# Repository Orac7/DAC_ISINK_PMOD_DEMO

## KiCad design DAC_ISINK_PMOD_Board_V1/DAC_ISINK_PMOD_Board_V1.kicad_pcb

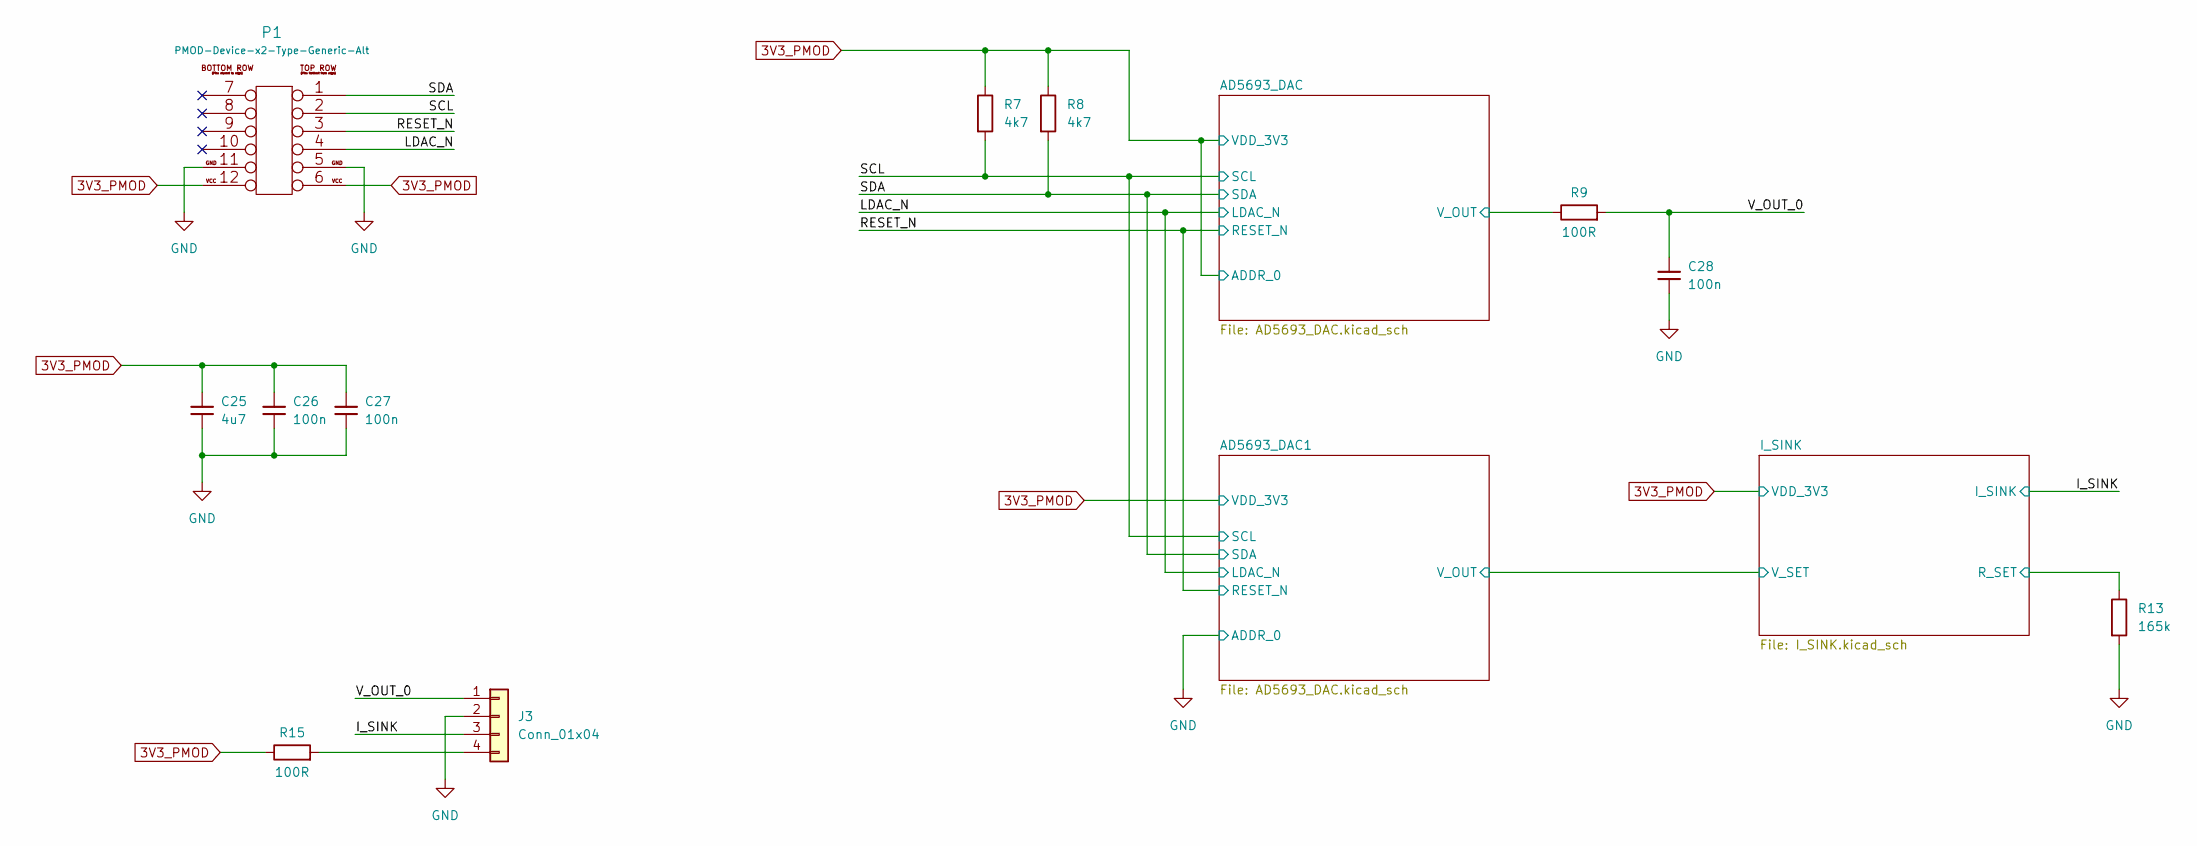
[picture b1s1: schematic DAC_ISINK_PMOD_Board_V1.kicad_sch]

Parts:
C25: 4u7; C_0603_1608Metric
C26, C27, C28: 100n; C_0603_1608Metric
J3: Conn_01x04; PhoenixContact_MC_1,5_4-G-3.5_1x04_P3.50mm_Horizontal
P1: PMOD-Device-x2-Type-Generic-Alt; pmod_pin_array_6x2
R7, R8: 4k7; R_0603_1608Metric
R9, R15: 100R; R_0603_1608Metric
R13: 165k; R_0603_1608Metric

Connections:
3V3_PMOD: C25.1, C26.1, C27.1, P1.6, P1.12, R7.1, R8.1, R15.1; also elsewhere on the board
/AD5693_DAC/V_OUT: R9.1; also elsewhere on the board
/I_SINK: J3.3; also elsewhere on the board
/I_SINK/R_SET: R13.1; also elsewhere on the board
/LDAC_N: P1.4; also elsewhere on the board
/RESET_N: P1.3; also elsewhere on the board
/SCL: P1.2, R7.2; also elsewhere on the board
/SDA: P1.1, R8.2; also elsewhere on the board
/V_OUT_0: C28.1, J3.1, R9.2
GND: C25.2, C26.2, C27.2, C28.2, J3.2, P1.5, P1.11, R13.2; also elsewhere on the board
unnamed: J3.4, R15.2

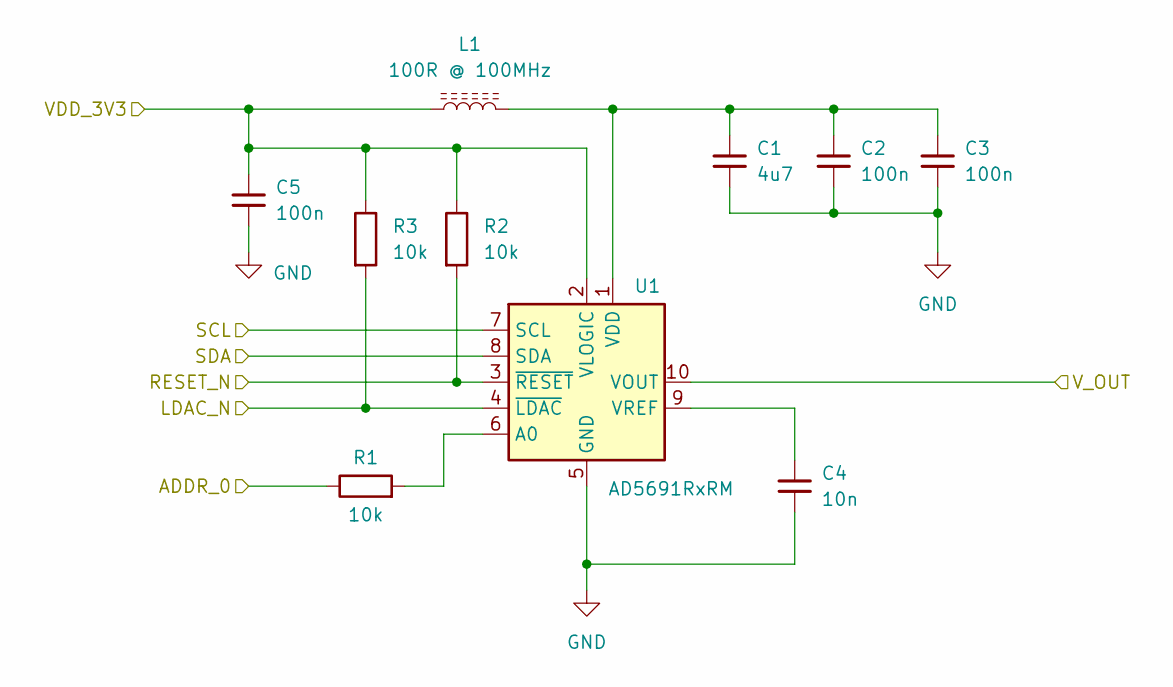
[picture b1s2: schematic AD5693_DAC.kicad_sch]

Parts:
C1: 4u7; C_0603_1608Metric
C2, C3, C5: 100n; C_0603_1608Metric
C4: 10n; C_0603_1608Metric
L1: 100R @ 100MHz; L_0603_1608Metric
R1, R2, R3: 10k; R_0603_1608Metric
U1: AD5691RxRM; MSOP-10_3x3mm_P0.5mm

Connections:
3V3_PMOD: C5.1, L1.1, R1.1, R2.1, R3.1, U1.2 (VLOGIC); also elsewhere on the board
/AD5693_DAC/V_OUT: U1.10 (VOUT); also elsewhere on the board
/LDAC_N: R3.2, U1.4 (~LDAC); also elsewhere on the board
/RESET_N: R2.2, U1.3 (~RESET); also elsewhere on the board
/SCL: U1.7 (SCL); also elsewhere on the board
/SDA: U1.8 (SDA); also elsewhere on the board
GND: C1.2, C2.2, C3.2, C4.2, C5.2, U1.5 (GND); also elsewhere on the board
unnamed: R1.2, U1.6 (A0)
unnamed: C1.1, C2.1, C3.1, L1.2, U1.1 (VDD)
unnamed: C4.1, U1.9 (VREF)

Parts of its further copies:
C6, C9, C10: 100n; C_0603_1608Metric
C7: 4u7; C_0603_1608Metric
C8: 10n; C_0603_1608Metric
L2: 100R @ 100MHz; L_0603_1608Metric
R4, R5, R6: 10k; R_0603_1608Metric
U2: AD5691RxRM; MSOP-10_3x3mm_P0.5mm

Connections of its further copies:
3V3_PMOD: C6.1, L2.1, R4.1, R6.1, U2.2 (VLOGIC); also elsewhere on the board
/AD5693_DAC1/V_OUT: U2.10 (VOUT); also elsewhere on the board
/LDAC_N: R4.2, U2.4 (~LDAC); also elsewhere on the board
/RESET_N: R6.2, U2.3 (~RESET); also elsewhere on the board
/SCL: U2.7 (SCL); also elsewhere on the board
/SDA: U2.8 (SDA); also elsewhere on the board
GND: C6.2, C7.2, C8.2, C9.2, C10.2, R5.1, U2.5 (GND); also elsewhere on the board
unnamed: R5.2, U2.6 (A0)
unnamed: C7.1, C9.1, C10.1, L2.2, U2.1 (VDD)
unnamed: C8.1, U2.9 (VREF)

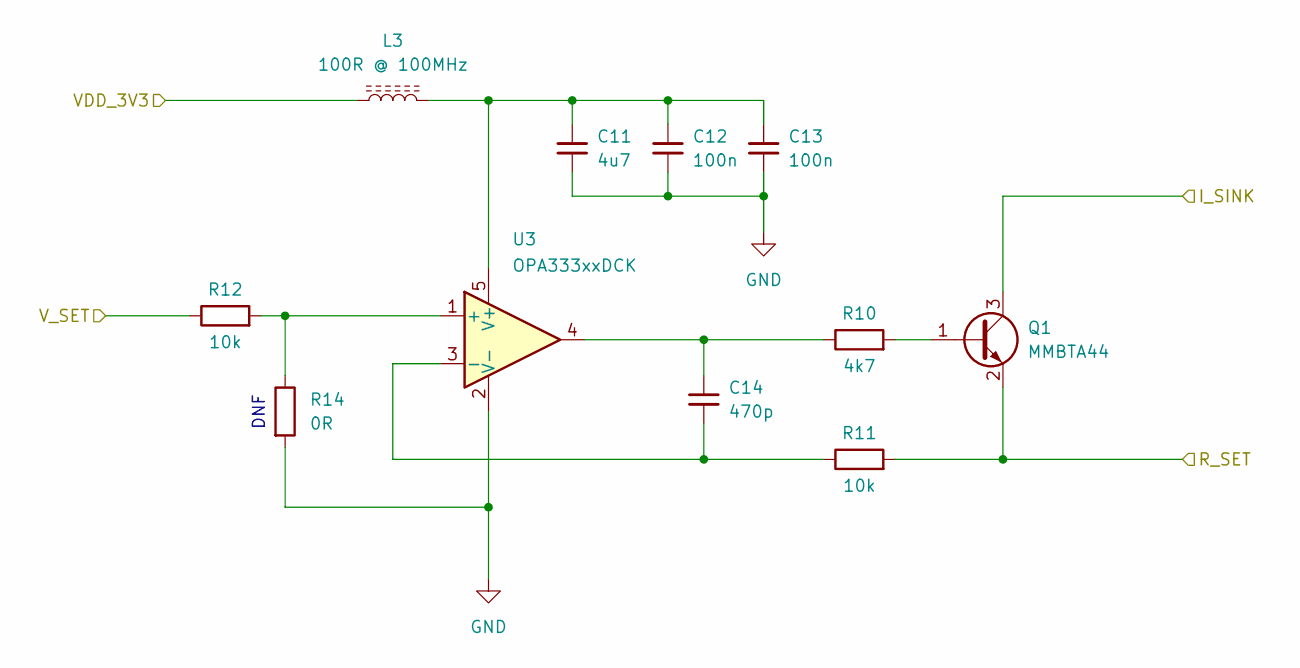
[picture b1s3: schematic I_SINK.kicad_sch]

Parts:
C11: 4u7; C_0603_1608Metric
C12, C13: 100n; C_0603_1608Metric
C14: 470p; C_0603_1608Metric
L3: 100R @ 100MHz; L_0603_1608Metric
Q1: MMBTA44; SOT-23
R10: 4k7; R_0603_1608Metric
R11, R12: 10k; R_0603_1608Metric
R14: 0R; R_0603_1608Metric
U3: OPA333xxDCK; SOT-353_SC-70-5

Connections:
3V3_PMOD: L3.1; also elsewhere on the board
/AD5693_DAC1/V_OUT: R12.1; also elsewhere on the board
/I_SINK: Q1.3 (C); also elsewhere on the board
/I_SINK/R_SET: Q1.2 (E), R11.2; also elsewhere on the board
GND: C11.2, C12.2, C13.2, R14.2, U3.2 (V-); also elsewhere on the board
unnamed: C14.1, R10.1, U3.4
unnamed: Q1.1 (B), R10.2
unnamed: R12.2, R14.1, U3.1 (+)
unnamed: C14.2, R11.1, U3.3 (-)
unnamed: C11.1, C12.1, C13.1, L3.2, U3.5 (V+)

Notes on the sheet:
DNF

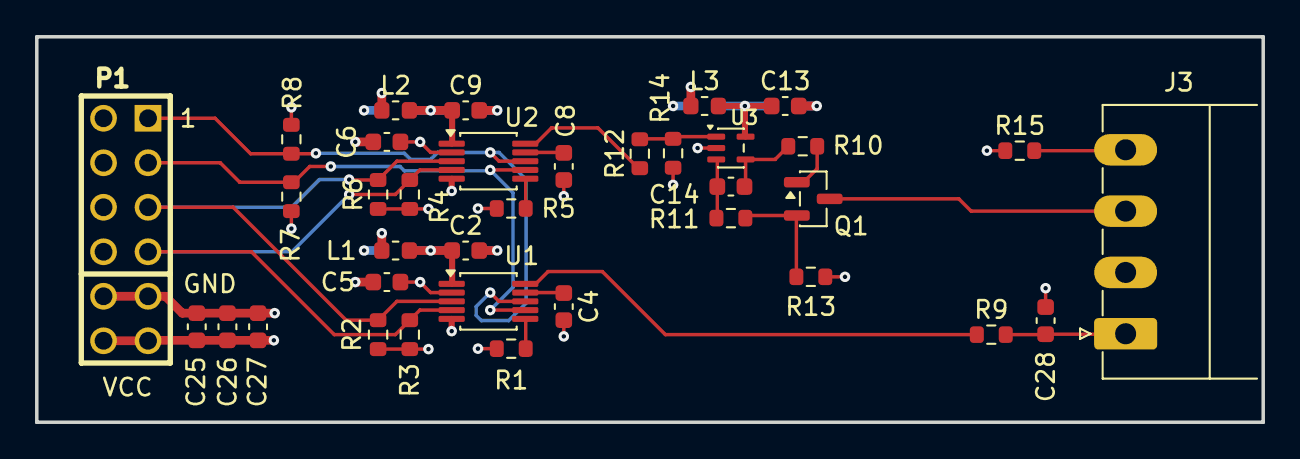
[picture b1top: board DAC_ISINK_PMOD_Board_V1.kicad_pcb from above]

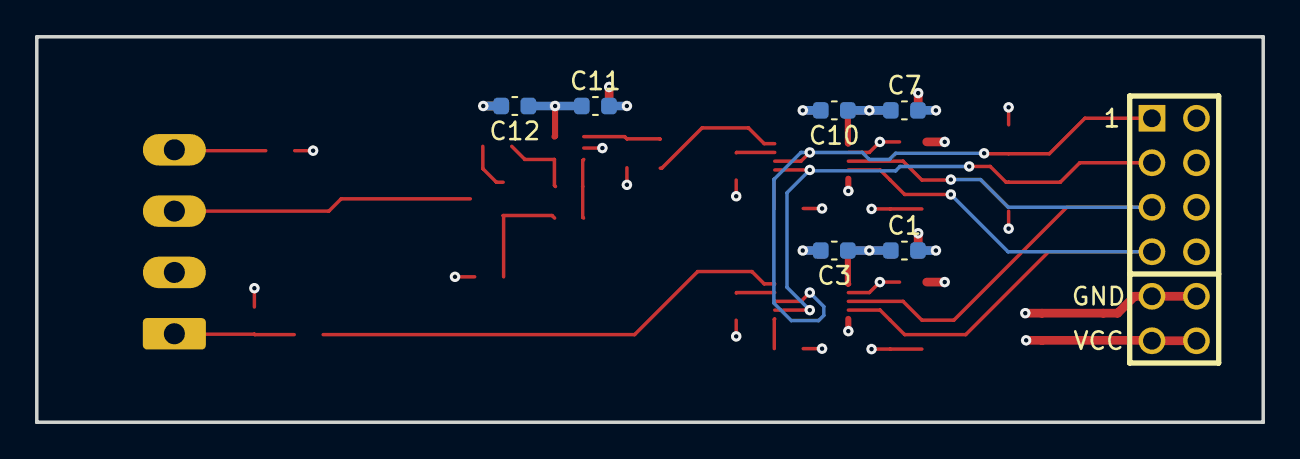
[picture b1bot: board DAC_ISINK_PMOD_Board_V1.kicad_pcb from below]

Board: 4 copper layers, 70.0 x 22.0 mm, 42 parts (6 on the bottom side), 23 nets.

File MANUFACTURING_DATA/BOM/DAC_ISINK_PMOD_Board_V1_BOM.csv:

"Reference","Qty","Value","DNP","Exclude from BOM","Exclude from Board","Exclude from Simulation","Exclude from Position Files","Footprint","Datasheet"
"C1,C7,C11,C25","4","4u7","","","","","${EXCLUDE_FROM_POS_FILES}","Capacitor_SMD:C_0603_1608Metric",""
"C2,C3,C5,C6,C9,C10,C12,C13,C26,C27,C28","11","100n","","","","","${EXCLUDE_FROM_POS_FILES}","Capacitor_SMD:C_0603_1608Metric",""
"C4,C8","2","10n","","","","","${EXCLUDE_FROM_POS_FILES}","Capacitor_SMD:C_0603_1608Metric",""
"C14","1","470p","","","","","${EXCLUDE_FROM_POS_FILES}","Capacitor_SMD:C_0603_1608Metric",""
"J3","1","Conn_01x04","","","","","${EXCLUDE_FROM_POS_FILES}","Connector_Phoenix_MC:PhoenixContact_MC_1,5_4-G-3.5_1x04_P3.50mm_Horizontal",""
"L1,L2,L3","3","100R @ 100MHz","","","","","${EXCLUDE_FROM_POS_FILES}","Inductor_SMD:L_0603_1608Metric",""
"P1","1","PMOD-Device-x2-Type-Generic-Alt","","","","","${EXCLUDE_FROM_POS_FILES}","klib_connectors:pmod_pin_array_6x2",""
"Q1","1","MMBTA44","","","","","${EXCLUDE_FROM_POS_FILES}","Package_TO_SOT_SMD:SOT-23","https://diotec.com/request/datasheet/mmbta42.pdf"
"R1,R2,R3,R4,R5,R6,R11,R12","8","10k","","","","","${EXCLUDE_FROM_POS_FILES}","Resistor_SMD:R_0603_1608Metric",""
"R7,R8,R10","3","4k7","","","","","${EXCLUDE_FROM_POS_FILES}","Resistor_SMD:R_0603_1608Metric",""
"R9,R15","2","100R","","","","","${EXCLUDE_FROM_POS_FILES}","Resistor_SMD:R_0603_1608Metric",""
"R13","1","165k","","","","","${EXCLUDE_FROM_POS_FILES}","Resistor_SMD:R_0603_1608Metric",""
"R14","1","0R","","","","","${EXCLUDE_FROM_POS_FILES}","Resistor_SMD:R_0603_1608Metric",""
"U1,U2","2","AD5691RxRM","","","","","${EXCLUDE_FROM_POS_FILES}","Package_SO:MSOP-10_3x3mm_P0.5mm","https://www.analog.com/media/en/technical-documentation/data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"
"U3","1","OPA333xxDCK","","","","","${EXCLUDE_FROM_POS_FILES}","Package_TO_SOT_SMD:SOT-353_SC-70-5","http://www.ti.com/lit/ds/symlink/opa333.pdf"
